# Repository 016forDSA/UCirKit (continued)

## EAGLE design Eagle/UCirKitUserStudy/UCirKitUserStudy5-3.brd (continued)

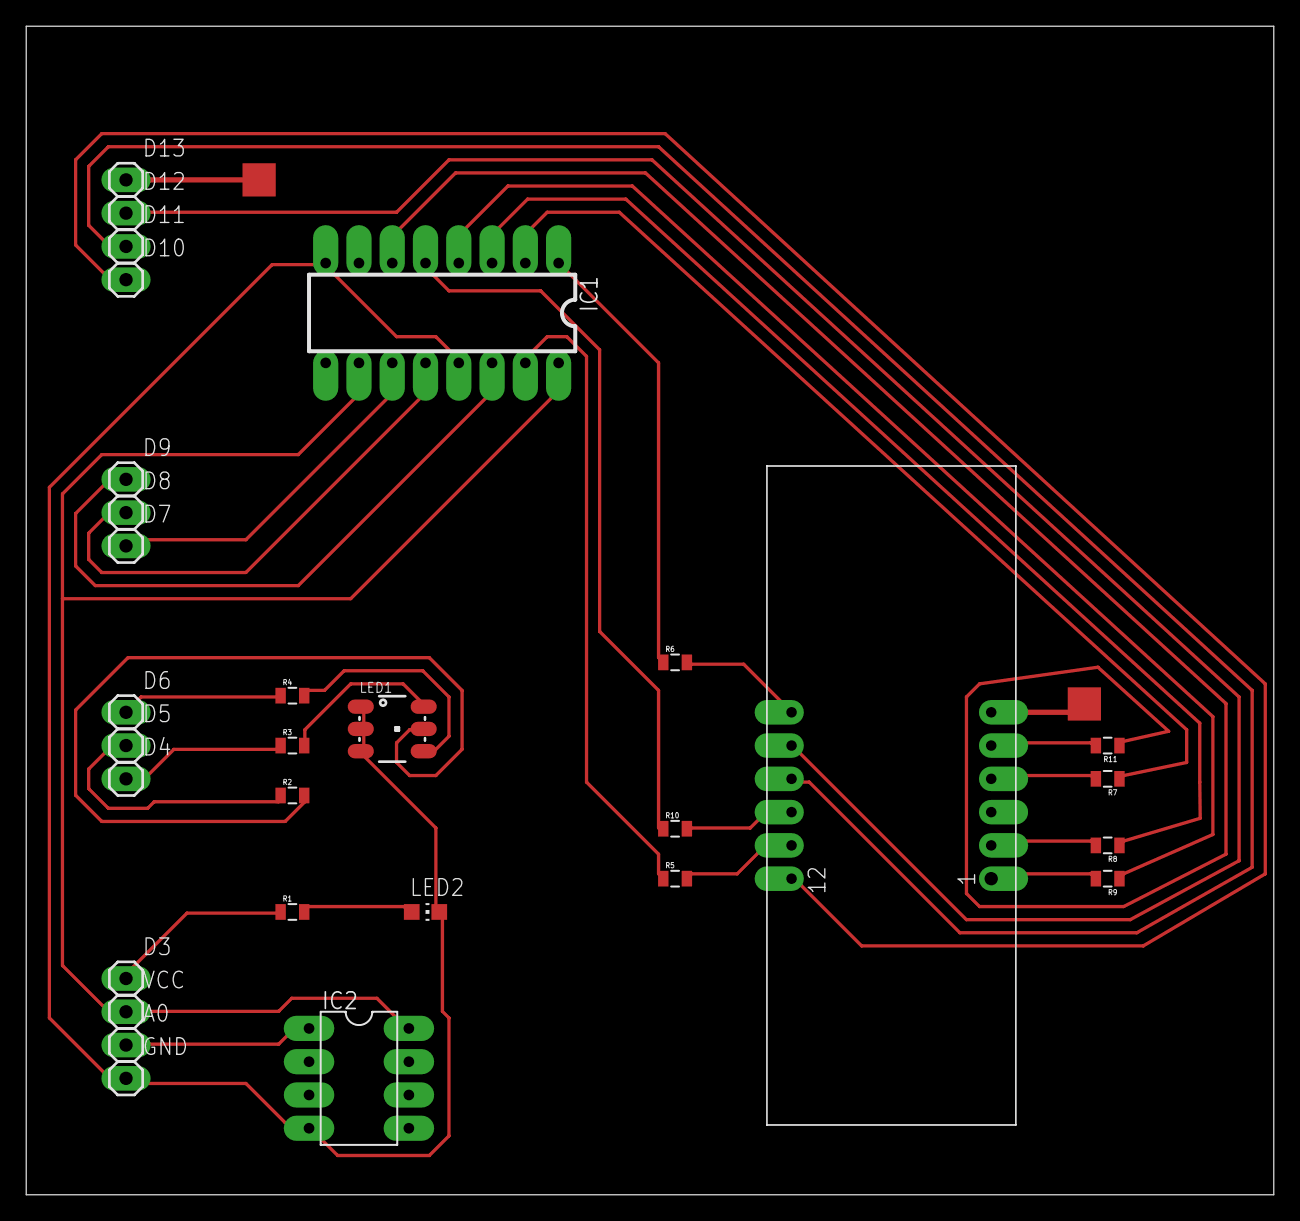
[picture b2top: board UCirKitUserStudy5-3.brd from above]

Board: 2 copper layers, 95.2 x 89.2 mm, 30 parts (0 on the bottom side), 32 nets.

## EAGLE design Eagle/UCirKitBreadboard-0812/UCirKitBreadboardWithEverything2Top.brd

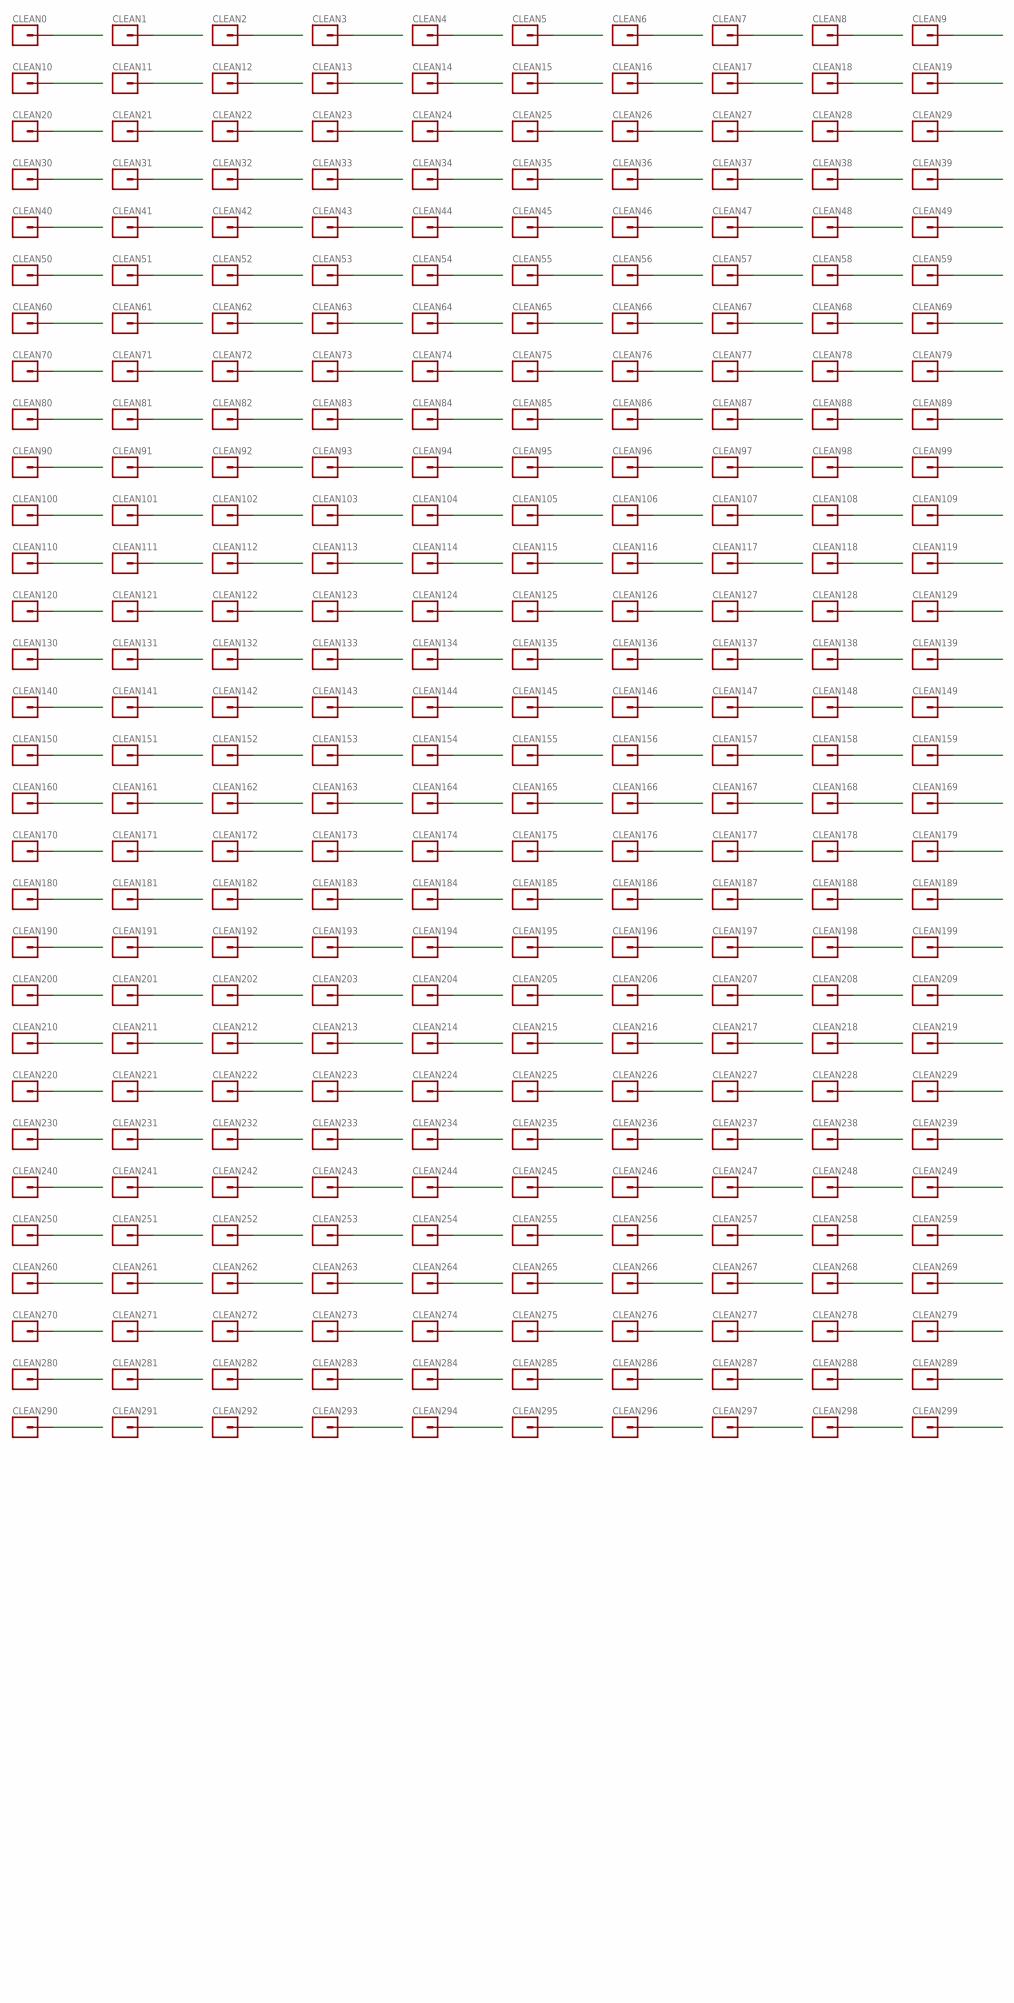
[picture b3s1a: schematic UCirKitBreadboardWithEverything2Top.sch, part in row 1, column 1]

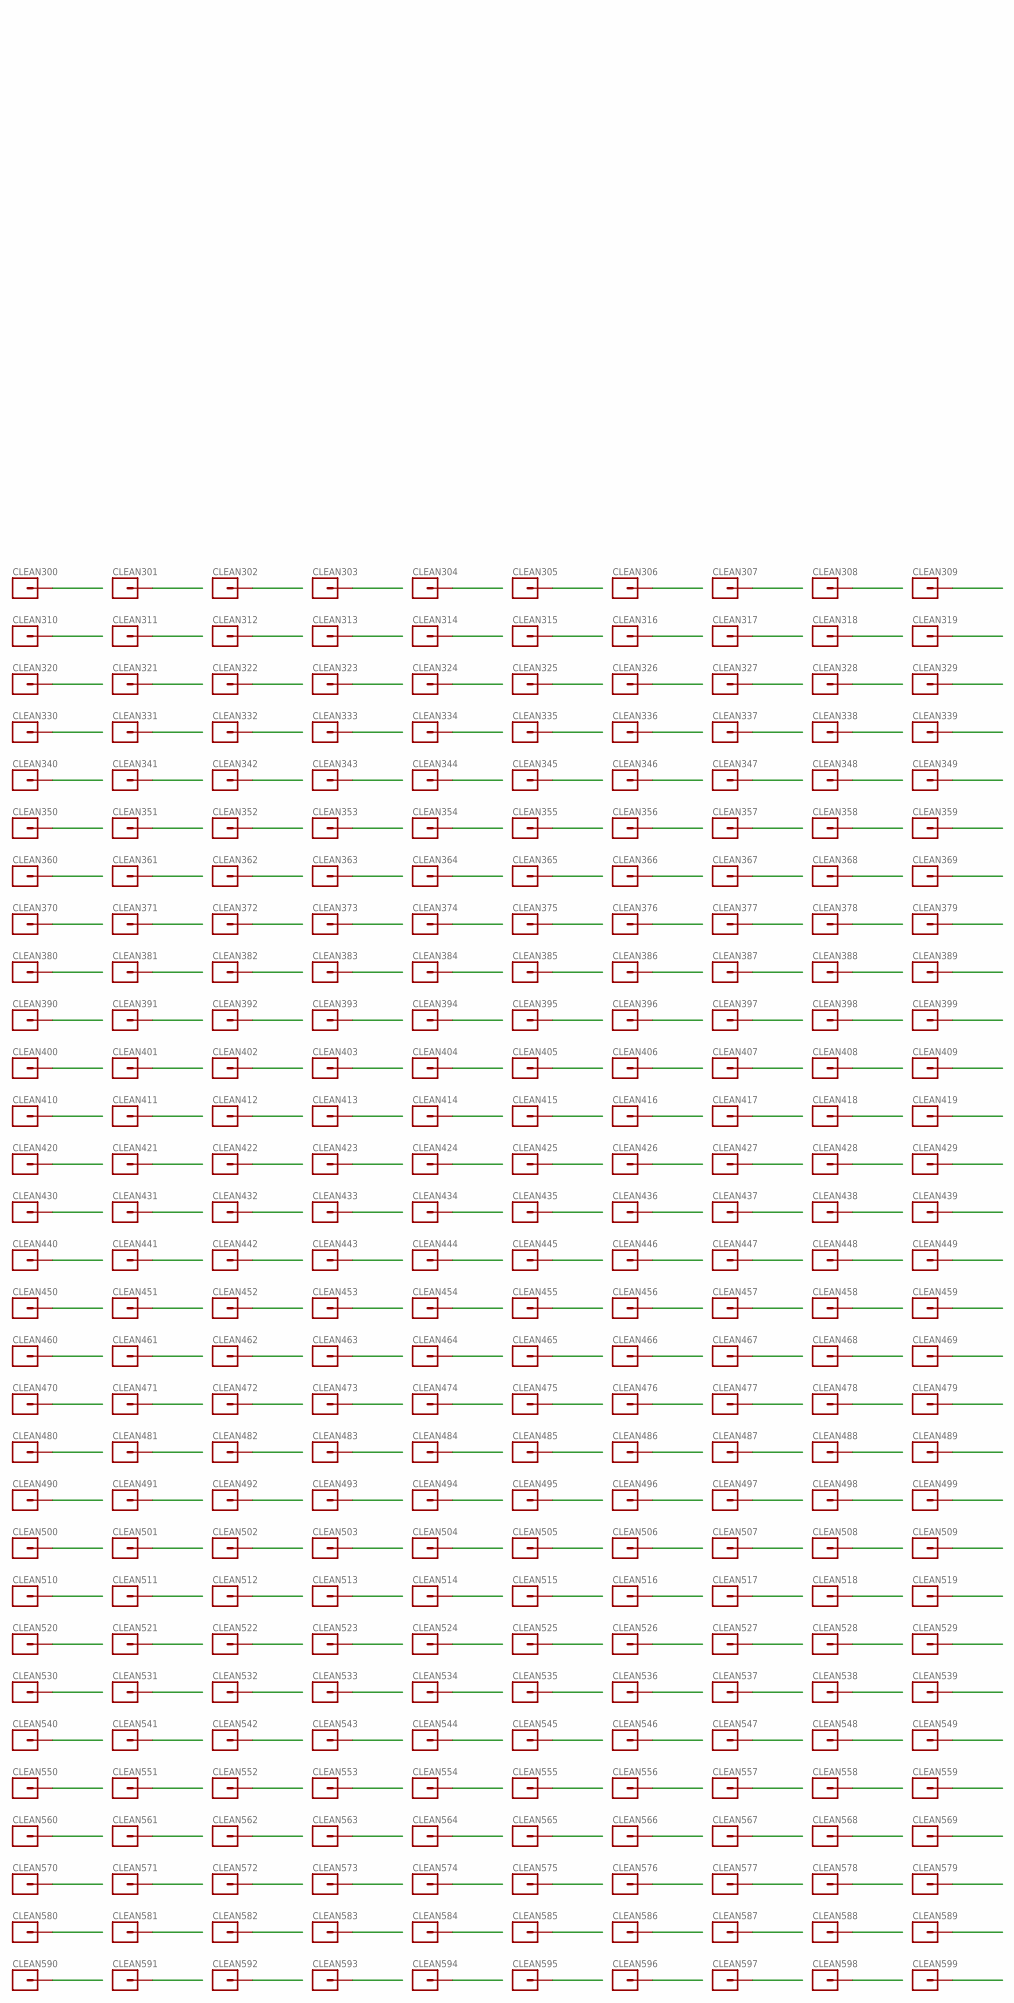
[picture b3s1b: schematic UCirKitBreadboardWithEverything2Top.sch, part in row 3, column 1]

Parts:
CLEAN0, CLEAN1, CLEAN2, CLEAN3, CLEAN4, CLEAN5, CLEAN6, CLEAN7, CLEAN8, CLEAN9, CLEAN10, CLEAN11, CLEAN12, CLEAN13, CLEAN14, CLEAN15, CLEAN16, CLEAN17, CLEAN18, CLEAN19, CLEAN20, CLEAN21, CLEAN22, CLEAN23, CLEAN24, CLEAN25, CLEAN26, CLEAN27, CLEAN28, CLEAN29, CLEAN30, CLEAN31, CLEAN32, CLEAN33, CLEAN34, CLEAN35, CLEAN36, CLEAN37, CLEAN38, CLEAN39, CLEAN40, CLEAN41, CLEAN42, CLEAN43, CLEAN44, CLEAN45, CLEAN46, CLEAN47, CLEAN48, CLEAN49, CLEAN50, CLEAN51, CLEAN52, CLEAN53, CLEAN54, CLEAN55, CLEAN56, CLEAN57, CLEAN58, CLEAN59, CLEAN60, CLEAN61, CLEAN62, CLEAN63, CLEAN64, CLEAN65, CLEAN66, CLEAN67, CLEAN68, CLEAN69, CLEAN70, CLEAN71, CLEAN72, CLEAN73, CLEAN74, CLEAN75, CLEAN76, CLEAN77, CLEAN78, CLEAN79, CLEAN80, CLEAN81, CLEAN82, CLEAN83, CLEAN84, CLEAN85, CLEAN86, CLEAN87, CLEAN88, CLEAN89, CLEAN90, CLEAN91, CLEAN92, CLEAN93, CLEAN94, CLEAN95, CLEAN96, CLEAN97, CLEAN98, CLEAN99, CLEAN100, CLEAN101, CLEAN102, CLEAN103, CLEAN104, CLEAN105, CLEAN106, CLEAN107, CLEAN108, CLEAN109, CLEAN110, CLEAN111, CLEAN112, CLEAN113, CLEAN114, CLEAN115, CLEAN116, CLEAN117, CLEAN118, CLEAN119, CLEAN120, CLEAN121, CLEAN122, CLEAN123, CLEAN124, CLEAN125, CLEAN126, CLEAN127, CLEAN128, CLEAN129, CLEAN130, CLEAN131, CLEAN132, CLEAN133, CLEAN134, CLEAN135, CLEAN136, CLEAN137, CLEAN138, CLEAN139, CLEAN140, CLEAN141, CLEAN142, CLEAN143, CLEAN144, CLEAN145, CLEAN146, CLEAN147, CLEAN148, CLEAN149, CLEAN150, CLEAN151, CLEAN152, CLEAN153, CLEAN154, CLEAN155, CLEAN156, CLEAN157, CLEAN158, CLEAN159, CLEAN160, CLEAN161, CLEAN162, CLEAN163, CLEAN164, CLEAN165, CLEAN166, CLEAN167, CLEAN168, CLEAN169, CLEAN170, CLEAN171, CLEAN172, CLEAN173, CLEAN174, CLEAN175, CLEAN176, CLEAN177, CLEAN178, CLEAN179, CLEAN180, CLEAN181, CLEAN182, CLEAN183, CLEAN184, CLEAN185, CLEAN186, CLEAN187, CLEAN188, CLEAN189, CLEAN190, CLEAN191, CLEAN192, CLEAN193, CLEAN194, CLEAN195, CLEAN196, CLEAN197, CLEAN198, CLEAN199, CLEAN200, CLEAN201, CLEAN202, CLEAN203, CLEAN204, CLEAN205, CLEAN206, CLEAN207, CLEAN208, CLEAN209, CLEAN210, CLEAN211, CLEAN212, CLEAN213, CLEAN214, CLEAN215, CLEAN216, CLEAN217, CLEAN218, CLEAN219, CLEAN220, CLEAN221, CLEAN222, CLEAN223, CLEAN224, CLEAN225, CLEAN226, CLEAN227, CLEAN228, CLEAN229, CLEAN230, CLEAN231, CLEAN232, CLEAN233, CLEAN234, CLEAN235, CLEAN236, CLEAN237, CLEAN238, CLEAN239, CLEAN240, CLEAN241, CLEAN242, CLEAN243, CLEAN244, CLEAN245, CLEAN246, CLEAN247, CLEAN248, CLEAN249, CLEAN250, CLEAN251, CLEAN252, CLEAN253, CLEAN254, CLEAN255, CLEAN256, CLEAN257, CLEAN258, CLEAN259, CLEAN260, CLEAN261, CLEAN262, CLEAN263, CLEAN264, CLEAN265, CLEAN266, CLEAN267, CLEAN268, CLEAN269, CLEAN270, CLEAN271, CLEAN272, CLEAN273, CLEAN274, CLEAN275, CLEAN276, CLEAN277, CLEAN278, CLEAN279, CLEAN280, CLEAN281, CLEAN282, CLEAN283, CLEAN284, CLEAN285, CLEAN286, CLEAN287, CLEAN288, CLEAN289, CLEAN290, CLEAN291, CLEAN292, CLEAN293, CLEAN294, CLEAN295, CLEAN296, CLEAN297, CLEAN298, CLEAN299: M01PTH_WITHOUT_TEXT; 1X01_WITHOUT_TEXT
CLEAN300, CLEAN301, CLEAN302, CLEAN303, CLEAN304, CLEAN305, CLEAN306, CLEAN307, CLEAN308, CLEAN309, CLEAN310, CLEAN311, CLEAN312, CLEAN313, CLEAN314, CLEAN315, CLEAN316, CLEAN317, CLEAN318, CLEAN319, CLEAN320, CLEAN321, CLEAN322, CLEAN323, CLEAN324, CLEAN325, CLEAN326, CLEAN327, CLEAN328, CLEAN329, CLEAN330, CLEAN331, CLEAN332, CLEAN333, CLEAN334, CLEAN335, CLEAN336, CLEAN337, CLEAN338, CLEAN339, CLEAN340, CLEAN341, CLEAN342, CLEAN343, CLEAN344, CLEAN345, CLEAN346, CLEAN347, CLEAN348, CLEAN349, CLEAN350, CLEAN351, CLEAN352, CLEAN353, CLEAN354, CLEAN355, CLEAN356, CLEAN357, CLEAN358, CLEAN359, CLEAN360, CLEAN361, CLEAN362, CLEAN363, CLEAN364, CLEAN365, CLEAN366, CLEAN367, CLEAN368, CLEAN369, CLEAN370, CLEAN371, CLEAN372, CLEAN373, CLEAN374, CLEAN375, CLEAN376, CLEAN377, CLEAN378, CLEAN379, CLEAN380, CLEAN381, CLEAN382, CLEAN383, CLEAN384, CLEAN385, CLEAN386, CLEAN387, CLEAN388, CLEAN389, CLEAN390, CLEAN391, CLEAN392, CLEAN393, CLEAN394, CLEAN395, CLEAN396, CLEAN397, CLEAN398, CLEAN399, CLEAN400, CLEAN401, CLEAN402, CLEAN403, CLEAN404, CLEAN405, CLEAN406, CLEAN407, CLEAN408, CLEAN409, CLEAN410, CLEAN411, CLEAN412, CLEAN413, CLEAN414, CLEAN415, CLEAN416, CLEAN417, CLEAN418, CLEAN419, CLEAN420, CLEAN421, CLEAN422, CLEAN423, CLEAN424, CLEAN425, CLEAN426, CLEAN427, CLEAN428, CLEAN429, CLEAN430, CLEAN431, CLEAN432, CLEAN433, CLEAN434, CLEAN435, CLEAN436, CLEAN437, CLEAN438, CLEAN439, CLEAN440, CLEAN441, CLEAN442, CLEAN443, CLEAN444, CLEAN445, CLEAN446, CLEAN447, CLEAN448, CLEAN449, CLEAN450, CLEAN451, CLEAN452, CLEAN453, CLEAN454, CLEAN455, CLEAN456, CLEAN457, CLEAN458, CLEAN459, CLEAN460, CLEAN461, CLEAN462, CLEAN463, CLEAN464, CLEAN465, CLEAN466, CLEAN467, CLEAN468, CLEAN469, CLEAN470, CLEAN471, CLEAN472, CLEAN473, CLEAN474, CLEAN475, CLEAN476, CLEAN477, CLEAN478, CLEAN479, CLEAN480, CLEAN481, CLEAN482, CLEAN483, CLEAN484, CLEAN485, CLEAN486, CLEAN487, CLEAN488, CLEAN489, CLEAN490, CLEAN491, CLEAN492, CLEAN493, CLEAN494, CLEAN495, CLEAN496, CLEAN497, CLEAN498, CLEAN499, CLEAN500, CLEAN501, CLEAN502, CLEAN503, CLEAN504, CLEAN505, CLEAN506, CLEAN507, CLEAN508, CLEAN509, CLEAN510, CLEAN511, CLEAN512, CLEAN513, CLEAN514, CLEAN515, CLEAN516, CLEAN517, CLEAN518, CLEAN519, CLEAN520, CLEAN521, CLEAN522, CLEAN523, CLEAN524, CLEAN525, CLEAN526, CLEAN527, CLEAN528, CLEAN529, CLEAN530, CLEAN531, CLEAN532, CLEAN533, CLEAN534, CLEAN535, CLEAN536, CLEAN537, CLEAN538, CLEAN539, CLEAN540, CLEAN541, CLEAN542, CLEAN543, CLEAN544, CLEAN545, CLEAN546, CLEAN547, CLEAN548, CLEAN549, CLEAN550, CLEAN551, CLEAN552, CLEAN553, CLEAN554, CLEAN555, CLEAN556, CLEAN557, CLEAN558, CLEAN559, CLEAN560, CLEAN561, CLEAN562, CLEAN563, CLEAN564, CLEAN565, CLEAN566, CLEAN567, CLEAN568, CLEAN569, CLEAN570, CLEAN571, CLEAN572, CLEAN573, CLEAN574, CLEAN575, CLEAN576, CLEAN577, CLEAN578, CLEAN579, CLEAN580, CLEAN581, CLEAN582, CLEAN583, CLEAN584, CLEAN585, CLEAN586, CLEAN587, CLEAN588, CLEAN589, CLEAN590, CLEAN591, CLEAN592, CLEAN593, CLEAN594, CLEAN595, CLEAN596, CLEAN597, CLEAN598, CLEAN599: M01PTH_SMD_3.25X0.85MM_NO_SILK; 1X01_SMD_3.25X0.85MM_NO_SILK

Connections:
NEW_0: CLEAN6.1, CLEAN360.P$3
NEW_1: CLEAN7.1, CLEAN361.P$3
NEW_2: CLEAN16.1, CLEAN362.P$3
NEW_3: CLEAN17.1, CLEAN363.P$3
NEW_4: CLEAN26.1, CLEAN364.P$3
NEW_5: CLEAN27.1, CLEAN365.P$3
NEW_6: CLEAN36.1, CLEAN366.P$3
NEW_7: CLEAN37.1, CLEAN367.P$3
NEW_8: CLEAN46.1, CLEAN368.P$3
NEW_9: CLEAN47.1, CLEAN369.P$3
NEW_10: CLEAN56.1, CLEAN370.P$3
NEW_11: CLEAN57.1, CLEAN371.P$3
NEW_12: CLEAN66.1, CLEAN372.P$3
NEW_13: CLEAN67.1, CLEAN373.P$3
NEW_14: CLEAN76.1, CLEAN374.P$3
NEW_15: CLEAN77.1, CLEAN375.P$3
NEW_16: CLEAN86.1, CLEAN376.P$3
NEW_17: CLEAN87.1, CLEAN377.P$3
NEW_18: CLEAN96.1, CLEAN378.P$3
NEW_19: CLEAN97.1, CLEAN379.P$3
NEW_20: CLEAN106.1, CLEAN380.P$3
NEW_21: CLEAN107.1, CLEAN381.P$3
NEW_22: CLEAN116.1, CLEAN382.P$3
NEW_23: CLEAN117.1, CLEAN383.P$3
NEW_24: CLEAN126.1, CLEAN384.P$3
NEW_25: CLEAN127.1, CLEAN385.P$3
NEW_26: CLEAN136.1, CLEAN386.P$3
NEW_27: CLEAN137.1, CLEAN387.P$3
NEW_28: CLEAN146.1, CLEAN388.P$3
NEW_29: CLEAN147.1, CLEAN389.P$3
NEW_30: CLEAN156.1, CLEAN390.P$3
NEW_31: CLEAN157.1, CLEAN391.P$3
NEW_32: CLEAN166.1, CLEAN392.P$3
NEW_33: CLEAN167.1, CLEAN393.P$3
NEW_34: CLEAN176.1, CLEAN394.P$3
NEW_35: CLEAN177.1, CLEAN395.P$3
NEW_36: CLEAN186.1, CLEAN396.P$3
NEW_37: CLEAN187.1, CLEAN397.P$3
NEW_38: CLEAN196.1, CLEAN398.P$3
NEW_39: CLEAN197.1, CLEAN399.P$3
NEW_40: CLEAN206.1, CLEAN400.P$3
NEW_41: CLEAN207.1, CLEAN401.P$3
NEW_42: CLEAN216.1, CLEAN402.P$3
NEW_43: CLEAN217.1, CLEAN403.P$3
NEW_44: CLEAN226.1, CLEAN404.P$3
NEW_45: CLEAN227.1, CLEAN405.P$3
NEW_46: CLEAN236.1, CLEAN406.P$3
NEW_47: CLEAN237.1, CLEAN407.P$3
NEW_48: CLEAN246.1, CLEAN408.P$3
NEW_49: CLEAN247.1, CLEAN409.P$3
NEW_50: CLEAN256.1, CLEAN410.P$3
NEW_51: CLEAN257.1, CLEAN411.P$3
NEW_52: CLEAN266.1, CLEAN412.P$3
NEW_53: CLEAN267.1, CLEAN413.P$3
NEW_54: CLEAN276.1, CLEAN414.P$3
NEW_55: CLEAN277.1, CLEAN415.P$3
NEW_56: CLEAN286.1, CLEAN416.P$3
NEW_57: CLEAN287.1, CLEAN417.P$3
NEW_58: CLEAN296.1, CLEAN418.P$3
NEW_59: CLEAN297.1, CLEAN419.P$3
NEW_60: CLEAN8.1, CLEAN420.P$3
NEW_61: CLEAN9.1, CLEAN421.P$3
NEW_62: CLEAN18.1, CLEAN422.P$3
NEW_63: CLEAN19.1, CLEAN423.P$3
NEW_64: CLEAN28.1, CLEAN424.P$3
NEW_65: CLEAN29.1, CLEAN425.P$3
NEW_66: CLEAN38.1, CLEAN426.P$3
NEW_67: CLEAN39.1, CLEAN427.P$3
NEW_68: CLEAN48.1, CLEAN428.P$3
NEW_69: CLEAN49.1, CLEAN429.P$3
NEW_70: CLEAN58.1, CLEAN430.P$3
NEW_71: CLEAN59.1, CLEAN431.P$3
NEW_72: CLEAN68.1, CLEAN432.P$3
NEW_73: CLEAN69.1, CLEAN433.P$3
NEW_74: CLEAN78.1, CLEAN434.P$3
NEW_75: CLEAN79.1, CLEAN435.P$3
NEW_76: CLEAN88.1, CLEAN436.P$3
NEW_77: CLEAN89.1, CLEAN437.P$3
NEW_78: CLEAN98.1, CLEAN438.P$3
NEW_79: CLEAN99.1, CLEAN439.P$3
NEW_80: CLEAN108.1, CLEAN440.P$3
NEW_81: CLEAN109.1, CLEAN441.P$3
NEW_82: CLEAN118.1, CLEAN442.P$3
NEW_83: CLEAN119.1, CLEAN443.P$3
NEW_84: CLEAN128.1, CLEAN444.P$3
NEW_85: CLEAN129.1, CLEAN445.P$3
NEW_86: CLEAN138.1, CLEAN446.P$3
NEW_87: CLEAN139.1, CLEAN447.P$3
NEW_88: CLEAN148.1, CLEAN448.P$3
NEW_89: CLEAN149.1, CLEAN449.P$3
NEW_90: CLEAN158.1, CLEAN450.P$3
NEW_91: CLEAN159.1, CLEAN451.P$3
NEW_92: CLEAN168.1, CLEAN452.P$3
NEW_93: CLEAN169.1, CLEAN453.P$3
NEW_94: CLEAN178.1, CLEAN454.P$3
NEW_95: CLEAN179.1, CLEAN455.P$3
NEW_96: CLEAN188.1, CLEAN456.P$3
NEW_97: CLEAN189.1, CLEAN457.P$3
NEW_98: CLEAN198.1, CLEAN458.P$3
NEW_99: CLEAN199.1, CLEAN459.P$3
NEW_100: CLEAN208.1, CLEAN460.P$3
NEW_101: CLEAN209.1, CLEAN461.P$3
NEW_102: CLEAN218.1, CLEAN462.P$3
NEW_103: CLEAN219.1, CLEAN463.P$3
NEW_104: CLEAN228.1, CLEAN464.P$3
NEW_105: CLEAN229.1, CLEAN465.P$3
NEW_106: CLEAN238.1, CLEAN466.P$3
NEW_107: CLEAN239.1, CLEAN467.P$3
NEW_108: CLEAN248.1, CLEAN468.P$3
NEW_109: CLEAN249.1, CLEAN469.P$3
NEW_110: CLEAN258.1, CLEAN470.P$3
NEW_111: CLEAN259.1, CLEAN471.P$3
NEW_112: CLEAN268.1, CLEAN472.P$3
NEW_113: CLEAN269.1, CLEAN473.P$3
NEW_114: CLEAN278.1, CLEAN474.P$3
NEW_115: CLEAN279.1, CLEAN475.P$3
NEW_116: CLEAN288.1, CLEAN476.P$3
NEW_117: CLEAN289.1, CLEAN477.P$3
NEW_118: CLEAN298.1, CLEAN478.P$3
NEW_119: CLEAN299.1, CLEAN479.P$3
NEW_120: CLEAN0.1, CLEAN300.P$3
NEW_121: CLEAN1.1, CLEAN301.P$3
NEW_122: CLEAN10.1, CLEAN302.P$3
NEW_123: CLEAN11.1, CLEAN303.P$3
NEW_124: CLEAN20.1, CLEAN304.P$3
NEW_125: CLEAN21.1, CLEAN305.P$3
NEW_126: CLEAN30.1, CLEAN306.P$3
NEW_127: CLEAN31.1, CLEAN307.P$3
NEW_128: CLEAN40.1, CLEAN308.P$3
NEW_129: CLEAN41.1, CLEAN309.P$3
NEW_130: CLEAN50.1, CLEAN310.P$3
NEW_131: CLEAN51.1, CLEAN311.P$3
NEW_132: CLEAN60.1, CLEAN312.P$3
NEW_133: CLEAN61.1, CLEAN313.P$3
NEW_134: CLEAN70.1, CLEAN314.P$3
NEW_135: CLEAN71.1, CLEAN315.P$3
NEW_136: CLEAN80.1, CLEAN316.P$3
NEW_137: CLEAN81.1, CLEAN317.P$3
NEW_138: CLEAN90.1, CLEAN318.P$3
NEW_139: CLEAN91.1, CLEAN319.P$3
NEW_140: CLEAN100.1, CLEAN320.P$3
NEW_141: CLEAN101.1, CLEAN321.P$3
NEW_142: CLEAN110.1, CLEAN322.P$3
NEW_143: CLEAN111.1, CLEAN323.P$3
NEW_144: CLEAN120.1, CLEAN324.P$3
NEW_145: CLEAN121.1, CLEAN325.P$3
NEW_146: CLEAN130.1, CLEAN326.P$3
NEW_147: CLEAN131.1, CLEAN327.P$3
NEW_148: CLEAN140.1, CLEAN328.P$3
NEW_149: CLEAN141.1, CLEAN329.P$3
NEW_150: CLEAN150.1, CLEAN330.P$3
NEW_151: CLEAN151.1, CLEAN331.P$3
NEW_152: CLEAN160.1, CLEAN332.P$3
NEW_153: CLEAN161.1, CLEAN333.P$3
NEW_154: CLEAN170.1, CLEAN334.P$3
NEW_155: CLEAN171.1, CLEAN335.P$3
NEW_156: CLEAN180.1, CLEAN336.P$3
NEW_157: CLEAN181.1, CLEAN337.P$3
NEW_158: CLEAN190.1, CLEAN338.P$3
NEW_159: CLEAN191.1, CLEAN339.P$3
NEW_160: CLEAN200.1, CLEAN340.P$3
NEW_161: CLEAN201.1, CLEAN341.P$3
NEW_162: CLEAN210.1, CLEAN342.P$3
NEW_163: CLEAN211.1, CLEAN343.P$3
NEW_164: CLEAN220.1, CLEAN344.P$3
NEW_165: CLEAN221.1, CLEAN345.P$3
NEW_166: CLEAN230.1, CLEAN346.P$3
NEW_167: CLEAN231.1, CLEAN347.P$3
NEW_168: CLEAN240.1, CLEAN348.P$3
NEW_169: CLEAN241.1, CLEAN349.P$3
NEW_170: CLEAN250.1, CLEAN350.P$3
NEW_171: CLEAN251.1, CLEAN351.P$3
NEW_172: CLEAN260.1, CLEAN352.P$3
NEW_173: CLEAN261.1, CLEAN353.P$3
NEW_174: CLEAN270.1, CLEAN354.P$3
NEW_175: CLEAN271.1, CLEAN355.P$3
NEW_176: CLEAN280.1, CLEAN356.P$3
NEW_177: CLEAN281.1, CLEAN357.P$3
NEW_178: CLEAN290.1, CLEAN358.P$3
NEW_179: CLEAN291.1, CLEAN359.P$3
NEW_180: CLEAN2.1, CLEAN480.P$3
NEW_181: CLEAN3.1, CLEAN481.P$3
NEW_182: CLEAN12.1, CLEAN482.P$3
NEW_183: CLEAN13.1, CLEAN483.P$3
NEW_184: CLEAN22.1, CLEAN484.P$3
NEW_185: CLEAN23.1, CLEAN485.P$3
NEW_186: CLEAN32.1, CLEAN486.P$3
NEW_187: CLEAN33.1, CLEAN487.P$3
NEW_188: CLEAN42.1, CLEAN488.P$3
NEW_189: CLEAN43.1, CLEAN489.P$3
NEW_190: CLEAN52.1, CLEAN490.P$3
NEW_191: CLEAN53.1, CLEAN491.P$3
NEW_192: CLEAN62.1, CLEAN492.P$3
NEW_193: CLEAN63.1, CLEAN493.P$3
NEW_194: CLEAN72.1, CLEAN494.P$3
NEW_195: CLEAN73.1, CLEAN495.P$3
NEW_196: CLEAN82.1, CLEAN496.P$3
NEW_197: CLEAN83.1, CLEAN497.P$3
NEW_198: CLEAN92.1, CLEAN498.P$3
NEW_199: CLEAN93.1, CLEAN499.P$3
NEW_200: CLEAN102.1, CLEAN500.P$3
NEW_201: CLEAN103.1, CLEAN501.P$3
NEW_202: CLEAN112.1, CLEAN502.P$3
NEW_203: CLEAN113.1, CLEAN503.P$3
NEW_204: CLEAN122.1, CLEAN504.P$3
NEW_205: CLEAN123.1, CLEAN505.P$3
NEW_206: CLEAN132.1, CLEAN506.P$3
NEW_207: CLEAN133.1, CLEAN507.P$3
NEW_208: CLEAN142.1, CLEAN508.P$3
NEW_209: CLEAN143.1, CLEAN509.P$3
NEW_210: CLEAN152.1, CLEAN510.P$3
NEW_211: CLEAN153.1, CLEAN511.P$3
NEW_212: CLEAN162.1, CLEAN512.P$3
NEW_213: CLEAN163.1, CLEAN513.P$3
NEW_214: CLEAN172.1, CLEAN514.P$3
NEW_215: CLEAN173.1, CLEAN515.P$3
NEW_216: CLEAN182.1, CLEAN516.P$3
NEW_217: CLEAN183.1, CLEAN517.P$3
NEW_218: CLEAN192.1, CLEAN518.P$3
NEW_219: CLEAN193.1, CLEAN519.P$3
NEW_220: CLEAN202.1, CLEAN520.P$3
NEW_221: CLEAN203.1, CLEAN521.P$3
NEW_222: CLEAN212.1, CLEAN522.P$3
NEW_223: CLEAN213.1, CLEAN523.P$3
NEW_224: CLEAN222.1, CLEAN524.P$3
NEW_225: CLEAN223.1, CLEAN525.P$3
NEW_226: CLEAN232.1, CLEAN526.P$3
NEW_227: CLEAN233.1, CLEAN527.P$3
NEW_228: CLEAN242.1, CLEAN528.P$3
NEW_229: CLEAN243.1, CLEAN529.P$3
NEW_230: CLEAN252.1, CLEAN530.P$3
NEW_231: CLEAN253.1, CLEAN531.P$3
NEW_232: CLEAN262.1, CLEAN532.P$3
NEW_233: CLEAN263.1, CLEAN533.P$3
NEW_234: CLEAN272.1, CLEAN534.P$3
NEW_235: CLEAN273.1, CLEAN535.P$3
NEW_236: CLEAN282.1, CLEAN536.P$3
NEW_237: CLEAN283.1, CLEAN537.P$3
NEW_238: CLEAN292.1, CLEAN538.P$3
NEW_239: CLEAN293.1, CLEAN539.P$3
NEW_240: CLEAN4.1, CLEAN560.P$3
NEW_241: CLEAN14.1, CLEAN561.P$3
NEW_242: CLEAN24.1, CLEAN562.P$3
NEW_243: CLEAN34.1, CLEAN563.P$3
NEW_244: CLEAN44.1, CLEAN564.P$3
NEW_245: CLEAN54.1, CLEAN565.P$3
NEW_246: CLEAN64.1, CLEAN566.P$3
NEW_247: CLEAN74.1, CLEAN567.P$3
NEW_248: CLEAN84.1, CLEAN568.P$3
NEW_249: CLEAN94.1, CLEAN569.P$3
NEW_250: CLEAN104.1, CLEAN570.P$3
NEW_251: CLEAN114.1, CLEAN571.P$3
NEW_252: CLEAN124.1, CLEAN572.P$3
NEW_253: CLEAN134.1, CLEAN573.P$3
NEW_254: CLEAN144.1, CLEAN574.P$3
NEW_255: CLEAN154.1, CLEAN575.P$3
NEW_256: CLEAN164.1, CLEAN576.P$3
NEW_257: CLEAN174.1, CLEAN577.P$3
NEW_258: CLEAN184.1, CLEAN578.P$3
NEW_259: CLEAN194.1, CLEAN579.P$3
NEW_260: CLEAN294.1, CLEAN590.P$3
NEW_261: CLEAN284.1, CLEAN591.P$3
NEW_262: CLEAN274.1, CLEAN592.P$3
NEW_263: CLEAN264.1, CLEAN593.P$3
NEW_264: CLEAN254.1, CLEAN594.P$3
NEW_265: CLEAN244.1, CLEAN595.P$3
NEW_266: CLEAN234.1, CLEAN596.P$3
NEW_267: CLEAN224.1, CLEAN597.P$3
NEW_268: CLEAN214.1, CLEAN598.P$3
NEW_269: CLEAN204.1, CLEAN599.P$3
NEW_270: CLEAN195.1, CLEAN540.P$3
NEW_271: CLEAN185.1, CLEAN541.P$3
NEW_272: CLEAN175.1, CLEAN542.P$3
NEW_273: CLEAN165.1, CLEAN543.P$3
NEW_274: CLEAN155.1, CLEAN544.P$3
NEW_275: CLEAN145.1, CLEAN545.P$3
NEW_276: CLEAN135.1, CLEAN546.P$3
NEW_277: CLEAN125.1, CLEAN547.P$3
NEW_278: CLEAN115.1, CLEAN548.P$3
NEW_279: CLEAN105.1, CLEAN549.P$3
NEW_280: CLEAN95.1, CLEAN550.P$3
NEW_281: CLEAN85.1, CLEAN551.P$3
NEW_282: CLEAN75.1, CLEAN552.P$3
NEW_283: CLEAN65.1, CLEAN553.P$3
NEW_284: CLEAN55.1, CLEAN554.P$3
NEW_285: CLEAN45.1, CLEAN555.P$3
NEW_286: CLEAN35.1, CLEAN556.P$3
NEW_287: CLEAN25.1, CLEAN557.P$3
NEW_288: CLEAN15.1, CLEAN558.P$3
NEW_289: CLEAN5.1, CLEAN559.P$3
NEW_290: CLEAN205.1, CLEAN580.P$3
NEW_291: CLEAN215.1, CLEAN581.P$3
NEW_292: CLEAN225.1, CLEAN582.P$3
NEW_293: CLEAN235.1, CLEAN583.P$3
NEW_294: CLEAN245.1, CLEAN584.P$3
NEW_295: CLEAN255.1, CLEAN585.P$3
NEW_296: CLEAN265.1, CLEAN586.P$3
NEW_297: CLEAN275.1, CLEAN587.P$3
NEW_298: CLEAN285.1, CLEAN588.P$3
NEW_299: CLEAN295.1, CLEAN589.P$3

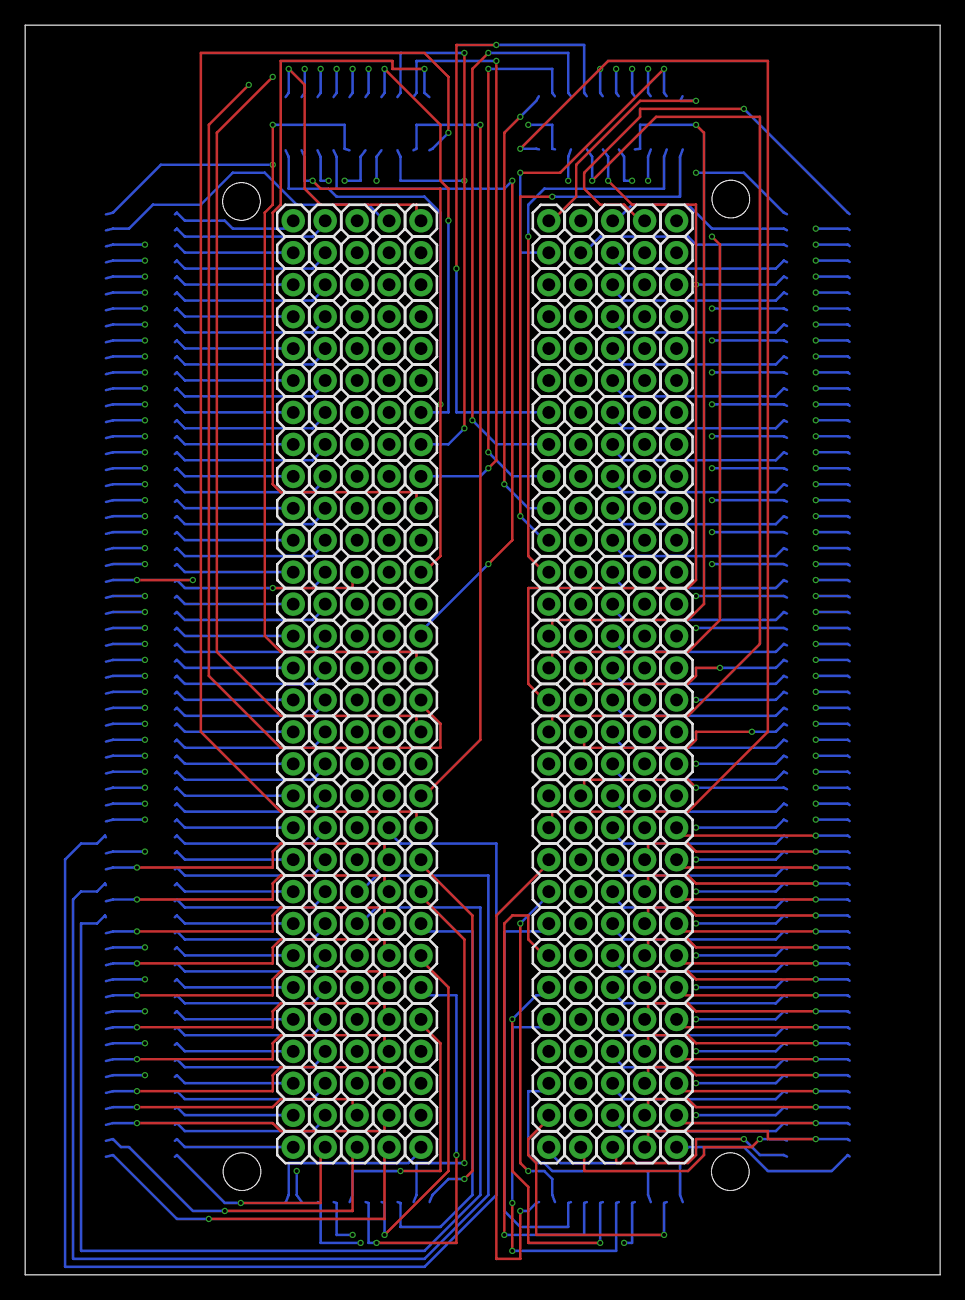
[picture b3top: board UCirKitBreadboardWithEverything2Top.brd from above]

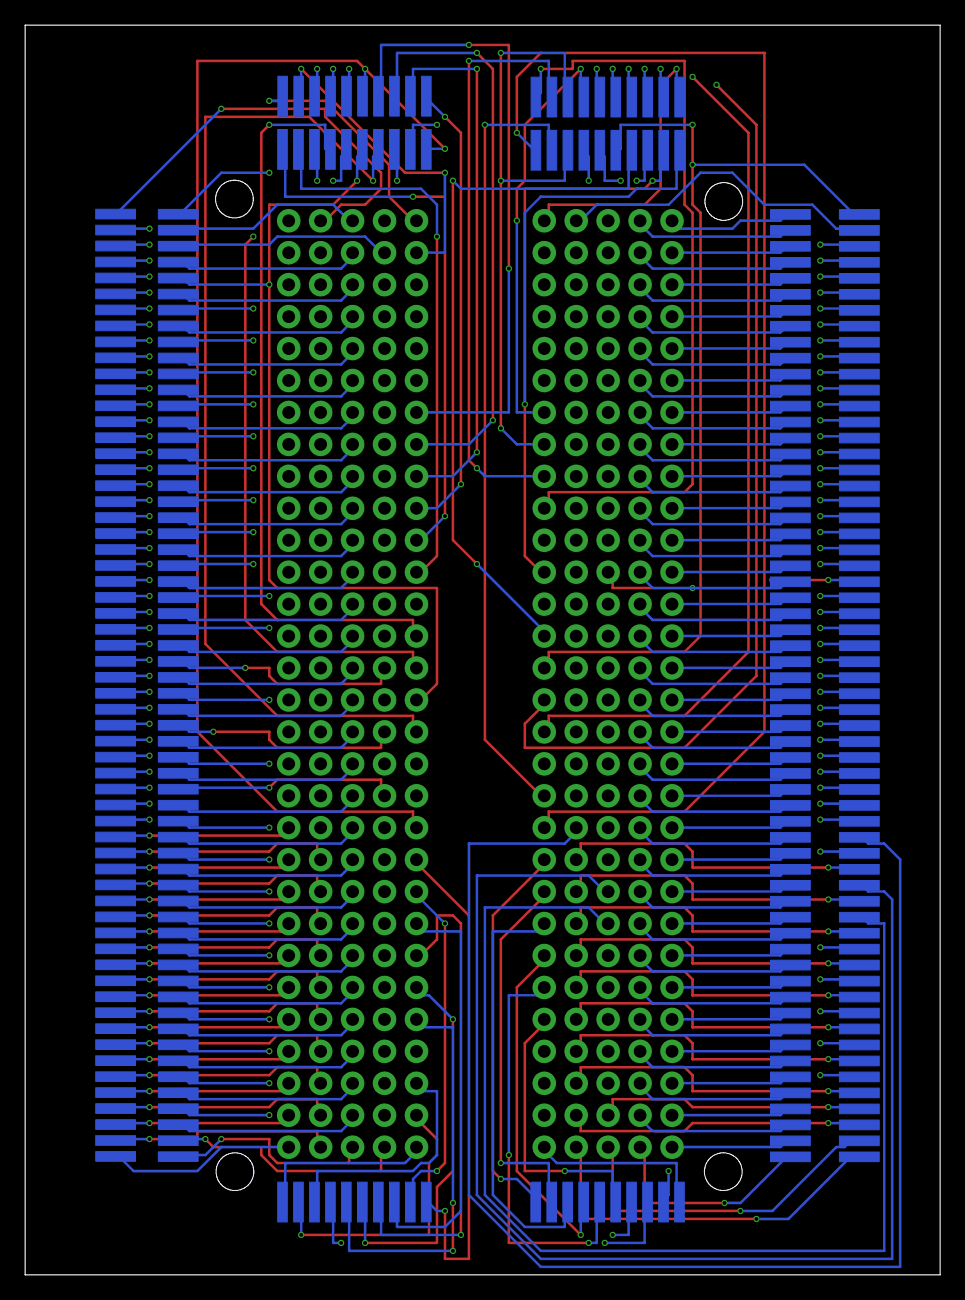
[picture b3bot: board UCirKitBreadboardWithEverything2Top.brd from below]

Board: 4 copper layers, 72.8 x 99.4 mm, 600 parts (300 on the bottom side), 300 nets.

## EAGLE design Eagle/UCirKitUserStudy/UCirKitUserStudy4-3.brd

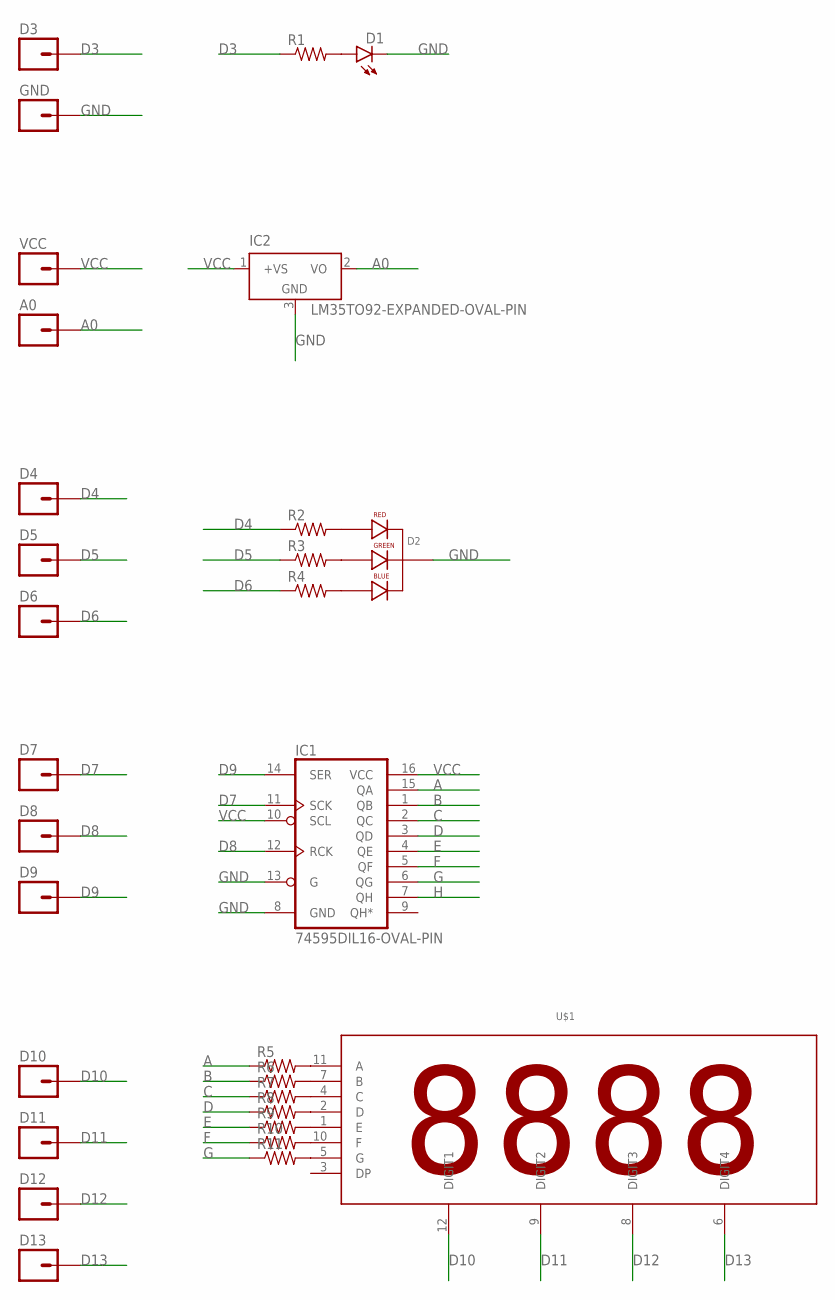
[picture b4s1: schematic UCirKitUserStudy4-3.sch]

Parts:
A0: M01OVAL_PIN; 1X01_OVAL_PIN
D1: LEDLED3MM-EXPANDED-OVAL-PIN; LED3MM-EXPANDED-OVAL-PIN
D2: LED-RGB-CC-THRULED-RGB-THRU-EXPANDED-OVAL-PIN; LED-RGB-THRU-EXPANDED-OVAL-PIN
D3, D4, D5, D6, D7, D8, D9, D10, D11, D12, D13: M01OVAL_PIN; 1X01_OVAL_PIN
GND: M01OVAL_PIN; 1X01_OVAL_PIN
IC1: 74595DIL16-OVAL-PIN; DIL16-OVAL-PIN
IC2: LM35TO92-EXPANDED-OVAL-PIN; TO92-EXPANDED-OVAL-PIN
R1, R2, R3, R4, R5, R6, R7, R8, R9, R10, R11: 1KOHM-1/4W-1%(PTH)PTH-EXPANDED-OVAL-PIN; PTH-EXPANDED-OVAL-PIN
U$1: 4DIGIT_SEVEN_SEGMENT4DIGIT_SEVEN_SEGMENT_OVAL_PIN; 4DIGIT_SEVEN_SEGMENT_OVAL_PIN
VCC: M01OVAL_PIN; 1X01_OVAL_PIN

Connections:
A: IC1.15 (QA), R5.P$1 (1)
A0: A0.1, IC2.2 (VO)
B: IC1.1 (QB), R6.P$1 (1)
C: IC1.2 (QC), R7.P$1 (1)
D: IC1.3 (QD), R8.P$1 (1)
D3: D3.1, R1.P$1 (1)
D4: D4.1, R2.P$1 (1)
D5: D5.1, R3.P$1 (1)
D6: D6.1, R4.P$1 (1)
D7: D7.1, IC1.11 (SCK)
D8: D8.1, IC1.12 (RCK)
D9: D9.1, IC1.14 (SER)
D10: D10.1, U$1.12 (DIGIT1)
D11: D11.1, U$1.9 (DIGIT2)
D12: D12.1, U$1.8 (DIGIT3)
D13: D13.1, U$1.6 (DIGIT4)
E: IC1.4 (QE), R9.P$1 (1)
F: IC1.5 (QF), R10.P$1 (1)
G: IC1.6 (QG), R11.P$1 (1)
GND: D1.K (C), D2.2 (CATHODE), GND.1, IC1.8 (GND), IC1.13 (G), IC2.3 (GND)
H: IC1.7 (QH)
unnamed: D1.A, R1.P$2 (2)
unnamed: D2.1 (RED_CATHODE), R2.P$2 (2)
unnamed: D2.3 (GREEN_CATHODE), R3.P$2 (2)
unnamed: D2.4 (BLUE_CATHODE), R4.P$2 (2)
unnamed: R5.P$2 (2), U$1.11 (A)
unnamed: R6.P$2 (2), U$1.7 (B)
unnamed: R7.P$2 (2), U$1.4 (C)
unnamed: R8.P$2 (2), U$1.2 (D)
unnamed: R9.P$2 (2), U$1.1 (E)
unnamed: R10.P$2 (2), U$1.10 (F)
unnamed: R11.P$2 (2), U$1.5 (G)
VCC: IC1.10 (SCL), IC1.16 (VCC), IC2.1 (+VS), VCC.1

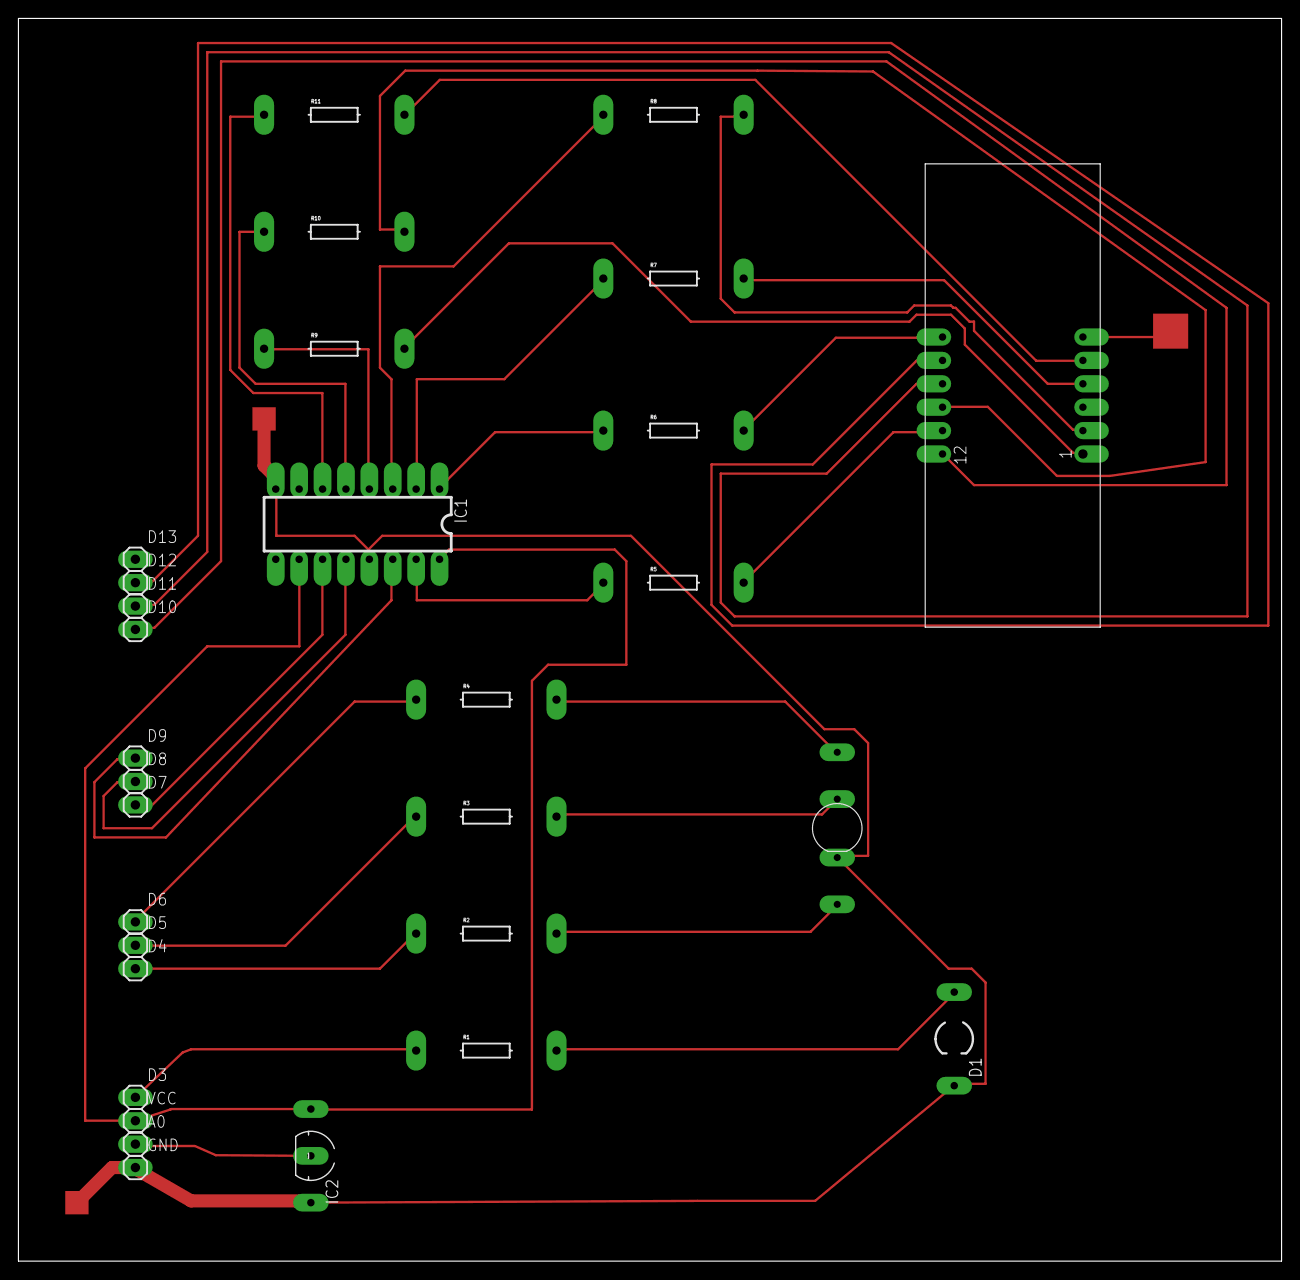
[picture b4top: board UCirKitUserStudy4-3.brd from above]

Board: 2 copper layers, 137.1 x 134.9 mm, 30 parts (0 on the bottom side), 32 nets.
